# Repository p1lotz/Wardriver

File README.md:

# Wardriver!

#

### wardriving (noun) - The act of searching for a Wi-Fi wireless network, usually from a moving vehicle, using a laptop or smartphone.
#

Hello yall! (My second README, have fun! <3) so this is a... wardriver! Well I like to call it a wi-fi/BLE scanner and monitor and I won't scan while from a moving vehicle but wardriver sounds cooler so yeah.
#
This is my second project which I actually did it all by myself (not unlike the software projects, let's not talk about those.)

This device scans wi-fi and bluetooth RFs and it also has GPS, and it uses the ESP32 Marauder (by justcallmekoko).

#
### This is the PCB 

you can find it in the repo files aswell (duh), along with the schematic, and all those files.

### This is the Schematic

#

#### I have also made an edit, which is on the *'doomscroller'* of Half-Life, as soon as I have a link (from anywhere) I will post it here. 

What else can I say, this project is a very interesting project and I am passionate on such things, on Radio Frequencies, scanning them, etc. and I have been wanting to make it for a long time. Its like when I think about it my heart starts racing with excitement! 

## NEW, THE ONE AND ONLY **ENCLOSUREEE**
Alright, I have made the enclosure too, took a bit, but its worth it, it looks LOVELYYY.
#
Images!
#

#

## Firmware

THE FIRMWARE. Yah the reviewer told me that I need it in here so here it is.

**ESP32 Marauder** by justcallmekoko
Source: https://github.com/justcallmekoko/ESP32Marauder
Pinned release: **v1.20.0**, 28 Oct 2026, https://github.com/justcallmekoko/ESP32Marauder/releases/tag/v1.20.0

### Pin mapping

| Module pad | GPIO | Net | Connects to |
|---|---|---|---|
| 3 | EN | RESET | SW2, reset button |
| 4 | GPIO4 | VBAT_SENSE | 100k/100k divider off BAT, ADC1_CH3 |
| 5 | GPIO5 | BTN_SEL | SW5, select |
| 6 | GPIO6 | BTN_BACK | SW6, back |
| 10 | GPIO17 | GPS_TX | NEO-M8N TX, so ESP receive |
| 11 | GPIO18 | GPS_RX | NEO-M8N RX, so ESP transmit |
| 12 | GPIO8 | SD_CS | microSD chip select on the display module |
| 13 | GPIO19 | USB_DN | USB-C D- |
| 14 | GPIO20 | USB_DP | USB-C D+ |
| 17 | GPIO9 | TFT_RST | ILI9341 reset |
| 18 | GPIO10 | TFT_CS | ILI9341 chip select |
| 19 | GPIO11 | MOSI | shared SPI, display and SD |
| 20 | GPIO12 | SCLK | shared SPI, display and SD |
| 21 | GPIO13 | MISO | shared SPI, display and SD |
| 22 | GPIO14 | TFT_DC | ILI9341 data/command |
| 23 | GPIO21 | TFT_LED | display backlight |
| 27 | GPIO0 | BOOT | SW1, boot button |
| 31 | GPIO38 | LED1 | status LED through 330R |
| 32 | GPIO39 | LED2 | status LED through 330R |
| 33 | GPIO40 | LED3 | status LED through 330R |
| 38 | GPIO2 | BTN_DOWN | SW4, down |
| 39 | GPIO1 | BTN_UP | SW3, up |

### Board config

```c
#define ILI9341_DRIVER
#define TFT_WIDTH  240
#define TFT_HEIGHT 320

#define TFT_MISO 13
#define TFT_MOSI 11
#define TFT_SCLK 12
#define TFT_CS   10
#define TFT_DC   14
#define TFT_RST   9
#define TFT_BL   21
#define TFT_BACKLIGHT_ON HIGH

#define SPI_FREQUENCY 40000000
```

Then a target block in `esp32_marauder/configs.h`.

```c
#ifdef MARAUDER_WARDRIVER
  #define HAS_BT
  #define HAS_BUTTONS
  #define HAS_SCREEN
  #define HAS_GPS
  #define HAS_SD
  #define USE_SD
  #define HAS_BATTERY
  #define BATTERY_ADC_PIN 4
  #define HAS_PSRAM
#endif

// buttons, all active low to GND with internal pullups
#ifdef MARAUDER_WARDRIVER
  #define U_BTN  1
  #define D_BTN  2
  #define C_BTN  5
  #define B_BTN  6
  #define L_BTN -1
  #define R_BTN -1
  #define HAS_U
  #define HAS_D
  #define HAS_C
  #define U_PULL true
  #define D_PULL true
  #define C_PULL true
  #define L_PULL true
  #define R_PULL true
#endif

// microSD shares the display SPI bus
#ifdef MARAUDER_WARDRIVER
  #define SD_CS 8
  #define SD_MISO TFT_MISO
  #define SD_MOSI TFT_MOSI
  #define SD_SCK  TFT_SCLK
#endif

// NEO-M8N on UART1, 9600 baud default
#ifdef MARAUDER_WARDRIVER
  #define GPS_SERIAL_INDEX 1
  #define GPS_TX 17
  #define GPS_RX 18
#endif
```

## And yes, of course, the BOM;
(BOM v1, I will cut costs to land under 65$, OR I will work more and make it fully finished for tier 3 of funding who knows :3)

|Part|Qty|Price|Link|
|---|---|---|---|
| ESP32-S3-WROOM-1U-N16R8 | 1 | $6.76/32.24 RON | https://www.digikey.com/en/products/detail/espressif-systems/ESP32-S3-WROOM-1U-N16R8/16162641 |
| 2.4GHz 3dBi Wi-Fi antenna + U.FL to RP-SMA cable | 1 | $2.20/10.50 RON | https://www.emag.ro/antena-wi-fi-2-4ghz-3dbi-cablu-ufl-ipx-rp-sma-ai1814/pd/D7RTGPYBM/ |
| 2.2" SPI TFT, ILI9341, 240×320, with microSD | 1 | $13.88/66.11 RON | https://www.amazon.com/Display-Module-240x320-ILI9341-Arduino/dp/B0F9XXV4V7?currency=USD |
| GY-NEO-M8N GPS module + patch antenna | 1 | $17.45 | https://www.addicore.com/products/neo-m8n-gps-gnss-module-with-eeprom |
| TP4056 Lithium Battery Charger Module with Dual Protection (USB-C) | 1 | $4.95/23.58 RON | https://www.crcibernetica.com/tp4056-lithium-battery-charger-module-with-dual-protection-usb-c/ | 
| AP2112K-3.3 | 1 | $0.17/0.81 RON | https://www.lcsc.com/product-detail/C51118.html |
| AO3401A | 1 | $0.52/2.48 RON| https://www.digikey.com/en/products/detail/alpha-omega-semiconductor-inc/AO3401A/1855773
| SS34 Schottky | 1 | $1.01/4.81 RON | https://www.digikey.com/en/products/detail/onsemi/SS34/1052384 |
| TYPE-C-31-M-12 | 1 | $0.19/0.90 RON | https://jlcpcb.com/partdetail/Korean_HropartsElec-TYPE_C_31_M12/ |
| Keystone 1042 18650 holder | 1 | $5.99/28.53 RON | https://www.digikey.com/en/products/detail/keystone-electronics/1042/2745668 | 
| Samsung INR18650-35E 3400mAh cell, flat top | 1 | $7.37/35.12 RON | https://botland.store/li-ion-batteries/15216-18650-li-ion-samsung-inr18650-35e-3400mah-5904422343071.html |
| B3S-1000 | 6(10 pack) | $4.24/20.20 RON| https://www.digikey.com/en/products/detail/aratas-formerly-omron-components/b3s-1000/20686
| slide switch, SPDT | 1 | $0.75/3.57RON | https://www.digikey.com/en/products/detail/c-k/OS102011MA1QN1/1981430 |
| LED 0805 | 3 | $0.38/1.81 RON | https://www.digikey.com/en/products/detail/visual-communications-company-vcc/LSM0805452V/10229619 | 
| 330 ohm resistor | 3 | $0.30/1.43 RON | https://www.digikey.com/en/products/detail/yageo/RC0805JR-07330RL/728311 |
| 10k ohm resistor | 3 | $0.33/1.57 RON | https://www.digikey.com/en/products/detail/vishay-dale/CRCW080510K0FKEAC/7928398 |
| 100k ohm resistor | 3 | $0.30/1.43 RON | https://www.digikey.com/en/products/detail/yageo/RC0805JR-07100KL/728239 |
| 5.1k ohm resistor | 2 | $0.2/0.95 RON | https://www.digikey.com/en/products/detail/yageo/RC0805JR-075K1L/728338 |
| 100nF capacitor | 4 | $0.72/3.43 RON | https://www.digikey.com/en/products/detail/kemet/C0805C104K5RACTU/411169
| 1uF capacitor | 1 | $0.67/3.19 RON | https://eu.mouser.com/en/ProductDetail/KYOCERA-AVX/KAF21KR71H105JU?qs=sGAEpiMZZMsh%252B1woXyUXjwCqkQtzlfA8HMiLPMH3N9o%3D |
| 10uF capacitor | 3 | $1.02/4.86 RON | https://www.digikey.com/en/products/detail/yageo/CC0805ZKY5V6BB106/2103093 |
| 22uF capacitor | 2 | $0.72/3.43 RON | https://www.digikey.com/en/products/detail/murata-electronics/GRM21BR61E226ME44L/4905535 |
| PCB from JLCPCB | 5 pack | $4.00/19.05 RON | N/A |

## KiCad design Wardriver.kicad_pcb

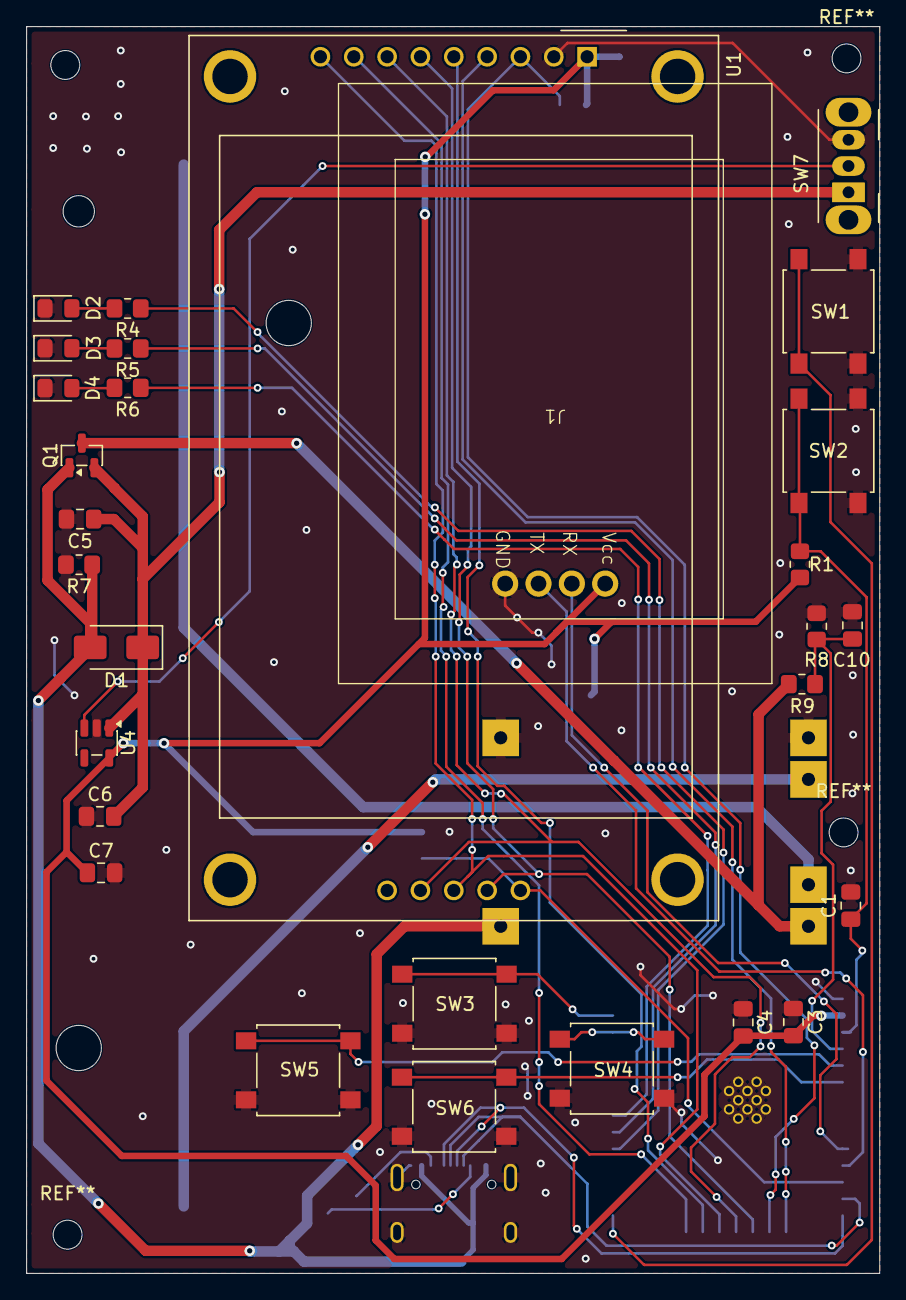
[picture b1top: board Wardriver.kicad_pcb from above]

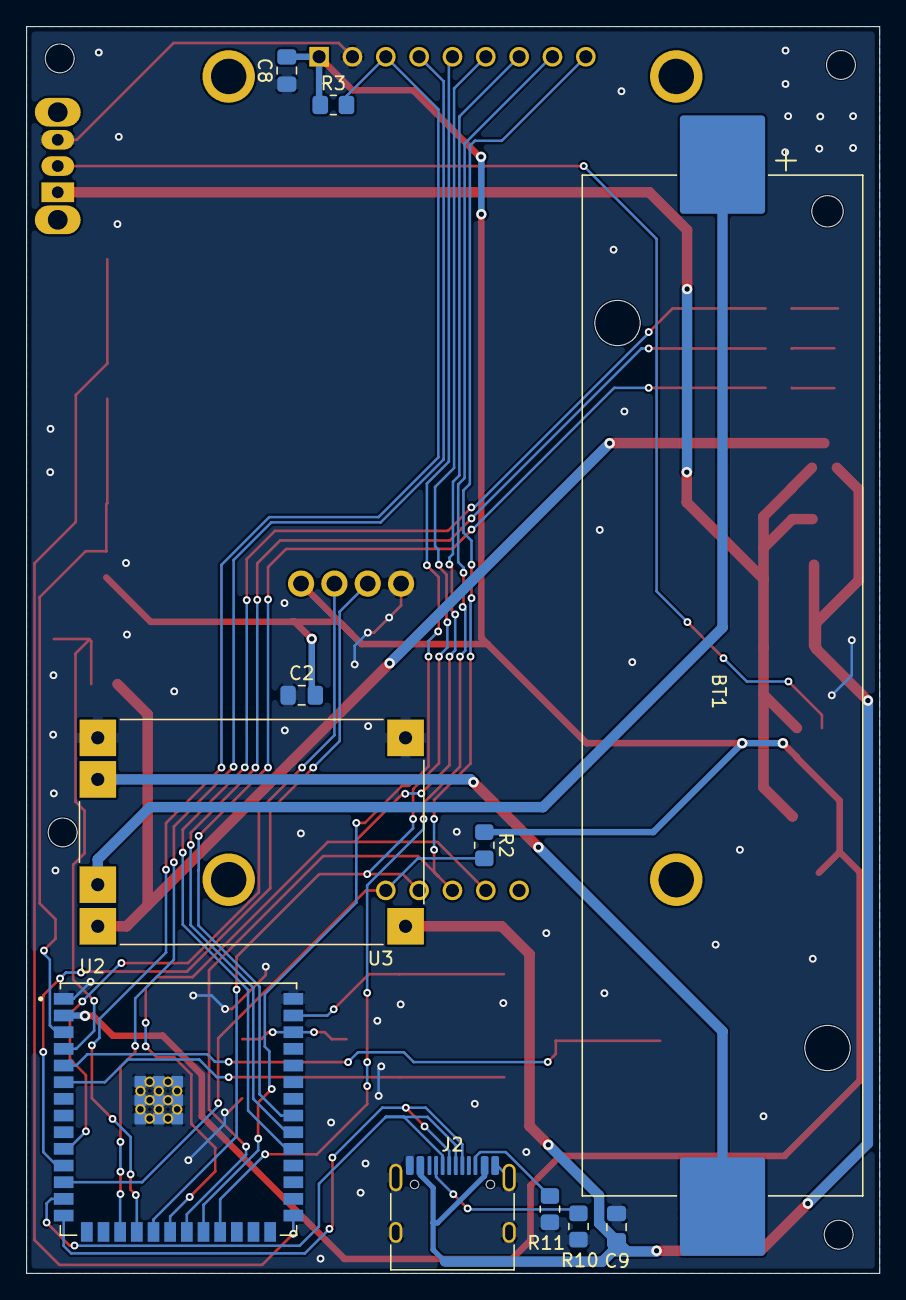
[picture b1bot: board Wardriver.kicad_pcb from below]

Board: 2 copper layers, 65.0 x 95.0 mm, 40 parts (11 on the bottom side), 35 nets.

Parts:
BT1: Battery; BatteryHolder_Keystone_1042_1x18650
C1: uF1; C_0805_2012Metric_Pad1.18x1.45mm_HandSolder
C2, C4, C8, C10: 100nF; C_0805_2012Metric_Pad1.18x1.45mm_HandSolder
C3, C5: 22uF; C_0805_2012Metric_Pad1.18x1.45mm_HandSolder
C6, C7: 10uF; C_0805_2012Metric_Pad1.18x1.45mm_HandSolder
C9: 10uF1; C_0805_2012Metric_Pad1.18x1.45mm_HandSolder
D1: SS34; D_SMA
D2, D3, D4: LED; LED_0805_2012Metric_Pad1.15x1.40mm_HandSolder
J1: GY-NEO-M8N
J2: USB_C_Receptacle_USB2.0_16P; USB_C_Receptacle_HRO_TYPE-C-31-M-12
Q1: AO3401A; SOT-23
R1, R2, R3: 10k; R_0805_2012Metric_Pad1.20x1.40mm_HandSolder
R4, R5, R6: 330; R_0805_2012Metric_Pad1.20x1.40mm_HandSolder
R7, R8, R9: 100k; R_0805_2012Metric_Pad1.20x1.40mm_HandSolder
R10, R11: 5.1k; R_0805_2012Metric_Pad1.20x1.40mm_HandSolder
SW1, SW2: SW_Push; SW_SPST_B3S-1000
SW3, SW4, SW5, SW6: Switch; SW_SPST_B3S-1000
SW7: slide switch; SW_Slide_SPDT_Angled_CK_OS102011MA1Q
U1: CR2013-MI2120
U2: ESP32-S3-WROOM-1U-N16R8; XCVR_ESP32-S3-WROOM-1U-N16R8
U3: TP4056_MICRO-USB_CHARGER_-_1A; MODULE_TP4056_MICRO-USB_CHARGER_-_1A
U4: AP2112K-3.3; SOT-23-5

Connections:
/3V3: C2.2, C3.2, C4.2, C7.1, C8.2, J1.1, R1.2, R2.1, R3.1, U1.1 (VCC), U2.2 (3V3), U4.5 (VOUT)
/BAT: Q1.3 (D), R9.1, U3.OUT_P (OUT+)
/BOOT: SW1.1, U2.27 (GPIO0/BOOT)
/BTN_BACK: SW6.1, U2.6 (GPIO6/TOUCH6/ADC1_CH5)
/BTN_DOWN: SW4.1, U2.38 (GPIO2/TOUCH2/ADC1_CH1)
/BTN_SEL: SW5.1, U2.5 (GPIO5/TOUCH5/ADC1_CH4)
/BTN_UP: SW3.1, U2.39 (GPIO1/TOUCH1/ADC1_CH0)
/GND: C1.2, C2.1, C3.1, C4.1, C5.2, C6.1, C7.2, C8.1, C9.1, C10.2, D2.1 (K), D3.1 (K), D4.1 (K), J1.4, J2.A1 (GND), J2.A12 (GND), J2.B1 (GND), J2.B12 (GND), J2.SH (SHIELD), R7.2, R8.2, R10.2, R11.2, SW1.2, SW2.2, SW3.2, SW4.2, SW5.2, SW6.2, SW7.3 (C), U1.2 (GND), U2.1 (GND), U2.40 (GND), U2.41 (GND), U3.IN_N (IN-), U3.OUT_N (OUT-), U4.2 (GND)
/GPS_RX: J1.3, U2.11 (GPIO18/U1RXD/ADC2_CH7/CLK_OUT3)
/GPS_TX: J1.2, U2.10 (GPIO17/U1TXD/ADC2_CH6)
/LED1: R4.1, U2.31 (GPIO38/FSPIWP/SUBSPIWP)
/LED2: R5.1, U2.32 (MTCK/GPIO39/CLK_OUT3/SUBSPICS1)
/LED3: R6.1, U2.33 (MTDO/GPIO40/CLK_OUT2)
/MISO: U1.9 (MISO), U1.12 (SD_MISO), U2.21 (GPIO13/TOUCH13/ADC2_CH2/FSPIQ/FSPIIO7/S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)
/MOSI: U1.6 (MOSI), U1.11 (SD_MOSI), U2.19 (GPIO11/TOUCH11/ADC2_CH0/FSPID/FSPIIO5/S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)
/RESET: C1.1, R1.1, SW2.1, U2.3 (EN)
/SCLK: U1.7 (SCK), U1.13 (SD_SCK), U2.20 (GPIO12/TOUCH12/ADC2_CH1/FSPICLK/FSPIIO6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)
/SD_CS: R2.2, U1.10 (SD_CS), U2.12 (GPIO8/TOUCH8/ADC1_CH7/SUBSPICS1)
/TFT_CS: R3.2, U1.3 (~CS), U2.18 (GPIO10/TOUCH10/ADC1_CH9/FSPICS0/FSPIIO4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)
/TFT_DC: U1.5 (D/~C), U2.22 (GPIO14/TOUCH14/ADC2_CH3/FSPIWP/FSPIDQS/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)
/TFT_LED: U1.8 (LED), U2.23 (GPIO21)
/TFT_RST: U1.4 (RESET), U2.17 (GPIO9/TOUCH9/ADC1_CH8/FSPIHD/SUBSPIHD)
/USB_DN: J2.A7 (D-), J2.B7 (D-), U2.13 (GPIO19/U1RTS/ADC2_CH8/CLK_OUT2/USB_D-)
/USB_DP: J2.A6 (D+), J2.B6 (D+), U2.14 (GPIO20/U1CTS/ADC2_CH9/CLK_OUT1/USB_D+)
/VBAT_SENSE: C10.1, R8.1, R9.2, U2.4 (GPIO4/TOUCH4/ADC1_CH3)
/VBUS: C9.2, D1.2 (A), J2.A4 (VBUS), J2.A9 (VBUS), J2.B4 (VBUS), J2.B9 (VBUS), Q1.1 (G), R7.1, U3.IN_P (IN+)
/VSYS: C5.1, C6.2, D1.1 (K), Q1.2 (S), SW7.1 (A), U4.1 (VIN)
unnamed: BT1.1 (+), U3.BAT_P (BAT+)
unnamed: BT1.2 (-), U3.BAT_N (BAT-)
unnamed: D2.2 (A), R4.2
unnamed: D3.2 (A), R5.2
unnamed: D4.2 (A), R6.2
unnamed: J2.A5 (CC1), R10.1
unnamed: J2.B5 (CC2), R11.1
unnamed: SW7.2 (B), U4.3 (EN)
